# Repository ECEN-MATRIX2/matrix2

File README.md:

# ECEN 403/404 Matrix 2 Electric Scooter

Shared repository for the Matrix 2 ECEN 403/404 senior design project.

## Repository structure

```text
firmware/
  comms/esp32/ESP32_MATRIX2_minimal_reader/  ESP32 comms board firmware
  motor/stm32/                             STM32 motor controller firmware (placeholder)
software/
  mobile-app/scooter-app/                   Mobile application
hardware/
  fpga/                                    FPGA PCB files (placeholder)
  motor/                                   Motor controller PCB files (placeholder)
  comms/                                   Comms board KiCad project
  matrix/                                  Matrix converter hardware and design files
```

The matrix hardware folder includes the existing ECEN 403 and 404 schematics and layouts, simulations, and transformer design documents.

Run mobile app commands from `software/mobile-app/scooter-app`.

## Team workflow

Create a branch for future work, commit your changes, and open a pull request before merging into `main`.

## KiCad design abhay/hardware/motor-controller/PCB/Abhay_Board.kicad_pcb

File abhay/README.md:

# Abhay - motor control and power distribution

| Folder | Contents |
| --- | --- |
| `firmware/NIU_Throttle_Comms_v4_3` | STM32F405 motor firmware, local GUI, tests and v4.3 binary |
| `firmware/NIU_ESP_Comms_v4_3` | Matching ESP32-S3 UART/BLE firmware and app protocol |
| `hardware/rev-o` | Rev O intermediate board: editable KiCad project, libraries, 3D models, BOM and manufacturing files |
| `hardware/motor-controller` | Final motor-control PCB and its original license |

## Working with this folder

Edit these repository copies for future revisions. The original lab folders are separate copies; edits there do not automatically appear here. In GitHub Desktop, select Matrix 2, review changes, commit, push the branch and open a pull request. Keep shared team files outside `abhay/` unchanged unless coordinating a team update.

## Firmware

These are the paired v4.3 sources, with sampled phase-current throttle control and acknowledged app fault-clear/enable commands. This firmware is not FOC. The ESP copy here is the matching motor-integration baseline; it does not replace the team's separate `firmware/comms/` project.

Open either firmware directory in VS Code with PlatformIO, or run `pio run` from that directory. This builds only. The STM32 project targets `genericSTM32F405RG`; the ESP project targets `esp32-s3-devkitc-1` with 4 MB flash. PlatformIO installs the pinned dependencies. The ESP's workstation-specific cache directory override was removed.

Run `python firmware/run_checks.py` for offline native and GUI tests. It needs Python 3 with Tkinter and a C++17 compiler (`g++` on PATH, or set `CXX` to its full path). No boards are accessed. The original `verification/verify.py` files are historical preservation audits: they additionally require older development folders not included in this repository. Use `run_checks.py` for checks in this clone.

Launch the local motor GUI with `firmware/NIU_Throttle_Comms_v4_3/Start Motor GUI.cmd`. Its hardware connection uses ST-Link/OpenOCD; see the project tools and `APP_CONTRACT.txt`. No firmware was flashed as part of this import.

The original release notes/manifests record the state at packaging time and are retained unchanged. The `binary/` folders contain the existing release binaries, not fresh builds from this import. ELF debug files, build caches and serial logs are omitted; the ESP historical manifest still lists the omitted ELF's checksum. Hardware validation is not implied by offline test results. The recent bench discrepancy between indicated supply voltage and MCU VM telemetry remains unresolved; this import does not change VM scaling or safety limits.

## KiCad

Use KiCad 9 and install its standard symbol, footprint and 3D-model libraries.

- Rev O: open `hardware/rev-o/NIU_Intermediate_RevO.kicad_pro`. Gerbers and drill files are in `Manufacturing/Gerbers`; assembly files are in `Manufacturing/Assembly`; the full purchasing BOM is in `Purchasing`. Read `FABRICATION.txt` and `BENCH_CHECKS.txt` before fabrication/assembly. Stock records and validation reports are dated snapshots.
- Motor controller: open `hardware/motor-controller/PCB/Abhay_Board.kicad_pro`. Electrical design and layout are unchanged. Only the two local library-table paths were corrected to the supplied `Abhay.pretty` and `Abhay.lib` files. The board references both `KICAD6_3DMODEL_DIR` and `KICAD9_3DMODEL_DIR`; configure the older variable to the installed standard 3D-model directory if needed.

The motor controller's inherited license and upstream README are included in its folder. Statements in the upstream README describe the original xESC project, not validation or ratings of this modified motor board or the current firmware.

`import_manifest.json` lists SHA-256 checksums for the imported source files and identifies the three packaging-only changes. No motor runtime source, PCB or schematic was changed.

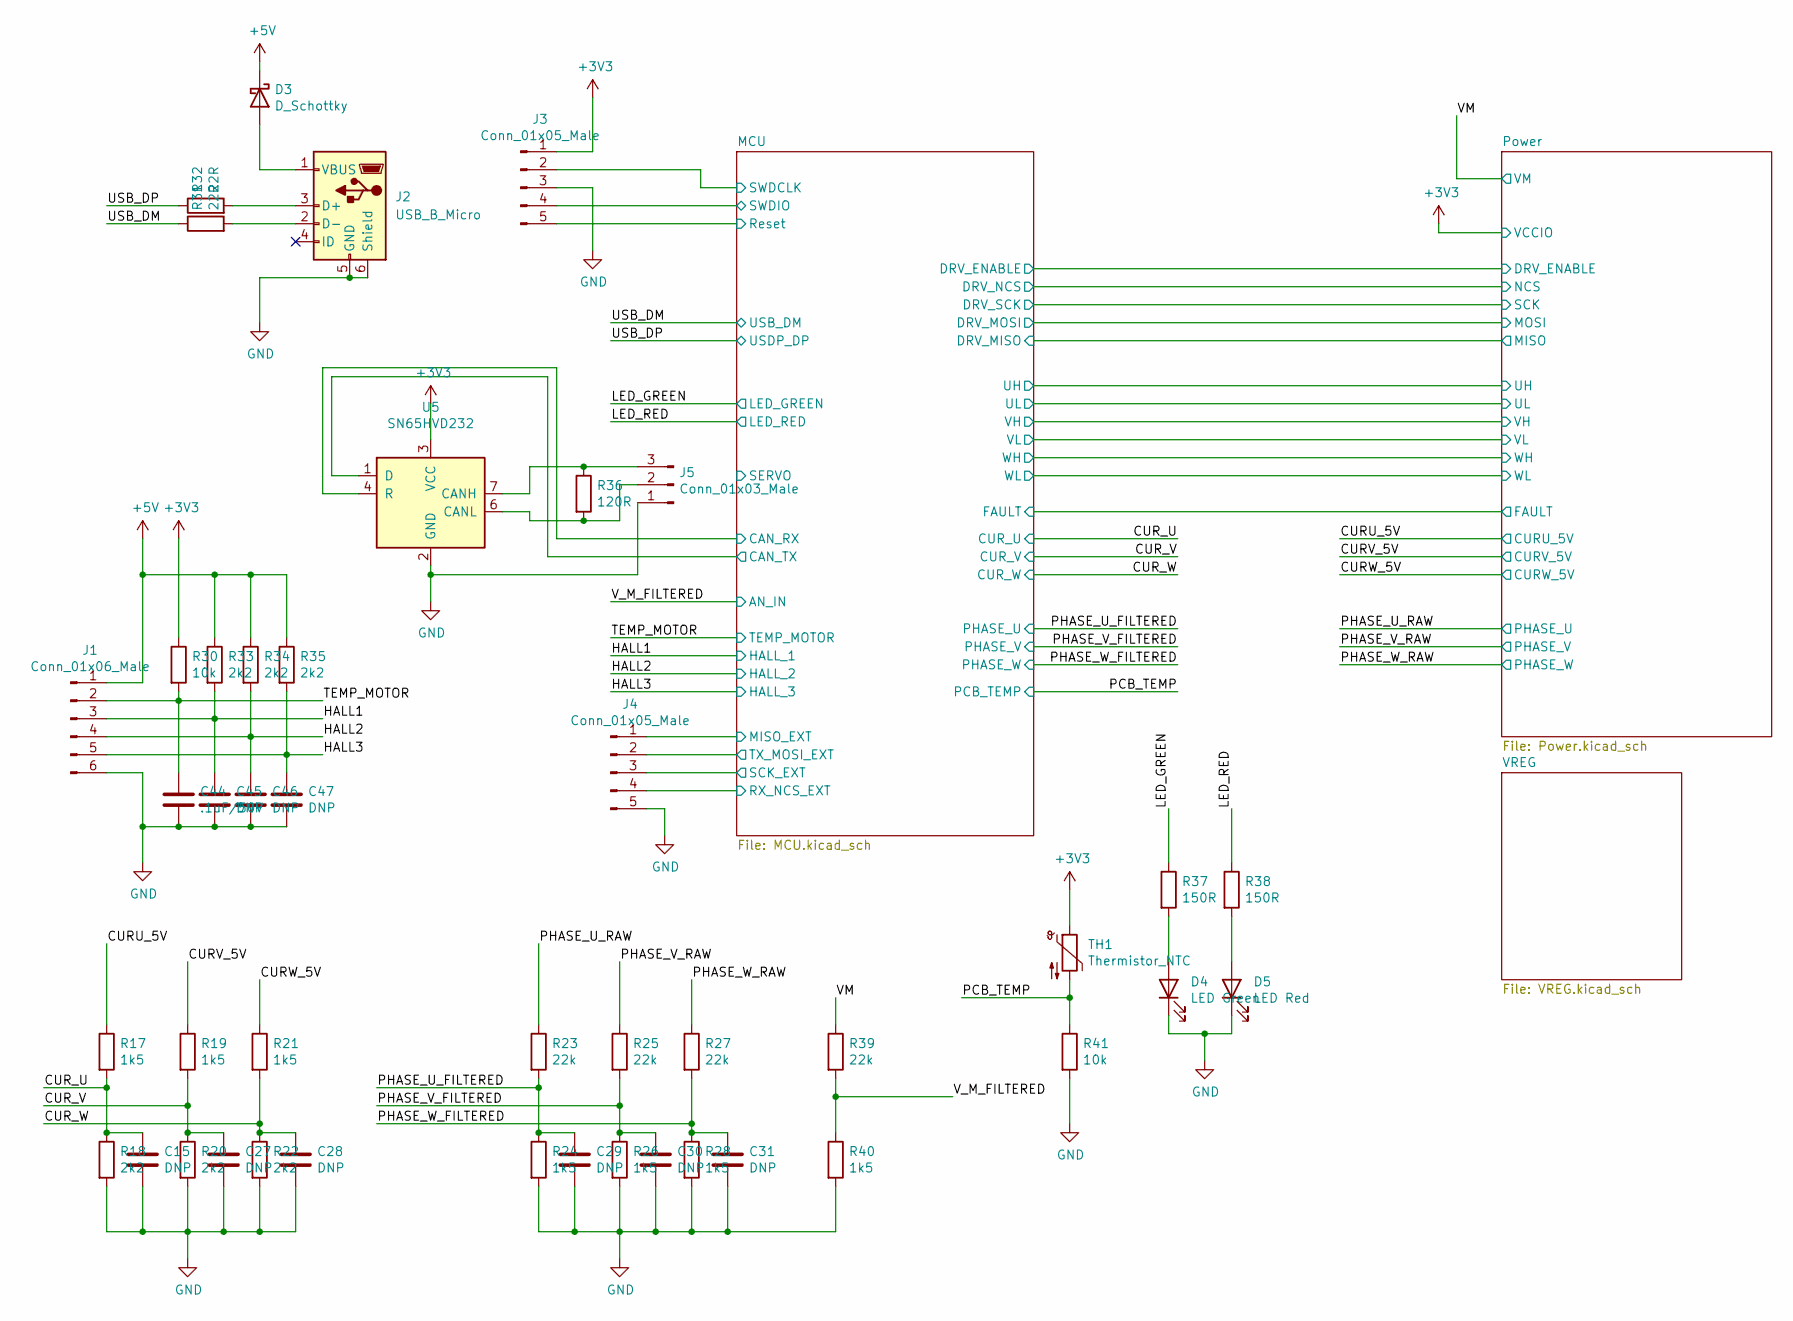
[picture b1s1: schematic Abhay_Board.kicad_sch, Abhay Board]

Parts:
C15, C27, C28, C29, C30, C31, C45, C46, C47: DNP; C_0603_1608Metric
C44: .1uF/50V; C_0603_1608Metric; Part Number CL10B104KC8NNNC; Digikey 1276-1935-1-ND
D3: D_Schottky; D_SOD-123; Part Number PMEG2010ER,115; Digikey 1727-5192-1-ND
D4: LED Green; LED_0603_1608Metric; Part Number LTST-C191KGKT; Digikey 160-1446-1-ND
D5: LED Red; LED_0603_1608Metric; Part Number LTST-C191KRKT; Digikey 160-1447-1-ND
J1: Conn_01x06_Male; PinHeader_1x06_P2.54mm_Vertical; Part Number DZ254R-11-06-63; LCSC C2935912
J2: USB_B_Micro; USB_Micro; JLC C145795
J3, J4: Conn_01x05_Male; PinHeader_1x05_P2.54mm_Vertical; Part Number DZ254R-11-05-63; LCSC C2935911
J5: Conn_01x03_Male; PinHeader_1x03_P2.54mm_Vertical; Part Number DZ254R-11-05-63; LCSC C2935909
R17, R19, R21, R24, R26, R28, R40: 1k5; R_0603_1608Metric; Part Number RC0603FR-071K5L; Digikey 311-1.50KHRCT-ND
R18, R20, R22, R33, R34, R35: 2k2; R_0603_1608Metric; Part Number RC0603FR-072K2L; Digikey 311-2.20KHRCT-ND
R23, R25, R27, R39: 22k; R_0603_1608Metric; Part Number RMCF0603FT22K0; Digikey RMCF0603FT22K0CT-ND
R30, R41: 10k; R_0603_1608Metric; Part Number RC0603FR-0710KL; Digikey 311-10.0KHRCT-ND
R31, R32: 22R; R_0603_1608Metric; Part Number RMCF0603FT22R0; Digikey RMCF0603FT22R0CT-ND
R36: 120R; R_0603_1608Metric; Part Number RMCF0603FT120R; Digikey RMCF0603FT120RCT-ND
R37, R38: 150R; R_0603_1608Metric; Part Number RC0603FR-07150RL; Digikey 311-150HRCT-ND
TH1: Thermistor_NTC; R_0603_1608Metric; Part Number NCU18XH103F60RB; Digikey 490-16279-1-ND
U5: SN65HVD232; SOIC-8_3.9x4.9mm_P1.27mm; Part Number SN65HVD232; Digikey 296-12282-5-ND

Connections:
+3V3: J3.1, R30.1, TH1.1, U5.3 (VCC); also elsewhere on the board
+5V: D3.1 (K), J1.1, R33.1, R34.1, R35.1; also elsewhere on the board
/CURU_5V: R17.1; also elsewhere on the board
/CURV_5V: R19.1; also elsewhere on the board
/CURW_5V: R21.1; also elsewhere on the board
/CUR_U: C15.1, R17.2, R18.1; also elsewhere on the board
/CUR_V: C27.1, R19.2, R20.1; also elsewhere on the board
/CUR_W: C28.1, R21.2, R22.1; also elsewhere on the board
/HALL1: C45.1, J1.3, R33.2; also elsewhere on the board
/HALL2: C46.1, J1.4, R34.2; also elsewhere on the board
/HALL3: C47.1, J1.5, R35.2; also elsewhere on the board
/LED_GREEN: R37.1; also elsewhere on the board
/LED_RED: R38.1; also elsewhere on the board
/MCU/CAN_RX: U5.4 (R); also elsewhere on the board
/MCU/CAN_TX: U5.1 (D); also elsewhere on the board
/MCU/MISO_EXT: J4.1; also elsewhere on the board
/MCU/RX_NCS_EXT: J4.4; also elsewhere on the board
/MCU/Reset: J3.5; also elsewhere on the board
/MCU/SCK_EXT: J4.3; also elsewhere on the board
/MCU/SWDCLK: J3.2; also elsewhere on the board
/MCU/SWDIO: J3.4; also elsewhere on the board
/MCU/TX_MOSI_EXT: J4.2; also elsewhere on the board
/PCB_TEMP: R41.1, TH1.2; also elsewhere on the board
/PHASE_U_FILTERED: C29.1, R23.2, R24.1; also elsewhere on the board
/PHASE_U_RAW: R23.1; also elsewhere on the board
/PHASE_V_FILTERED: C30.1, R25.2, R26.1; also elsewhere on the board
/PHASE_V_RAW: R25.1; also elsewhere on the board
/PHASE_W_FILTERED: C31.1, R27.2, R28.1; also elsewhere on the board
/PHASE_W_RAW: R27.1; also elsewhere on the board
/TEMP_MOTOR: C44.1, J1.2, R30.2; also elsewhere on the board
/USB_DM: R31.1; also elsewhere on the board
/USB_DP: R32.1; also elsewhere on the board
/VM: R39.1; also elsewhere on the board
/V_M_FILTERED: R39.2, R40.1; also elsewhere on the board
GND: C15.2, C27.2, C28.2, C29.2, C30.2, C31.2, C44.2, C45.2, C46.2, C47.2, D4.1 (K), D5.1 (K), J1.6, J2.5 (GND), J2.6 (Shield), J3.3, J4.5, J5.1, R18.2, R20.2, R22.2, R24.2, R26.2, R28.2, R40.2, R41.2, U5.2 (GND); also elsewhere on the board
unnamed: D3.2 (A), J2.1 (VBUS)
unnamed: D4.2 (A), R37.2
unnamed: D5.2 (A), R38.2
unnamed: J2.3 (D+), R32.2
unnamed: J2.2 (D-), R31.2
unnamed: J5.2, R36.2, U5.6 (CANL)
unnamed: J5.3, R36.1, U5.7 (CANH)

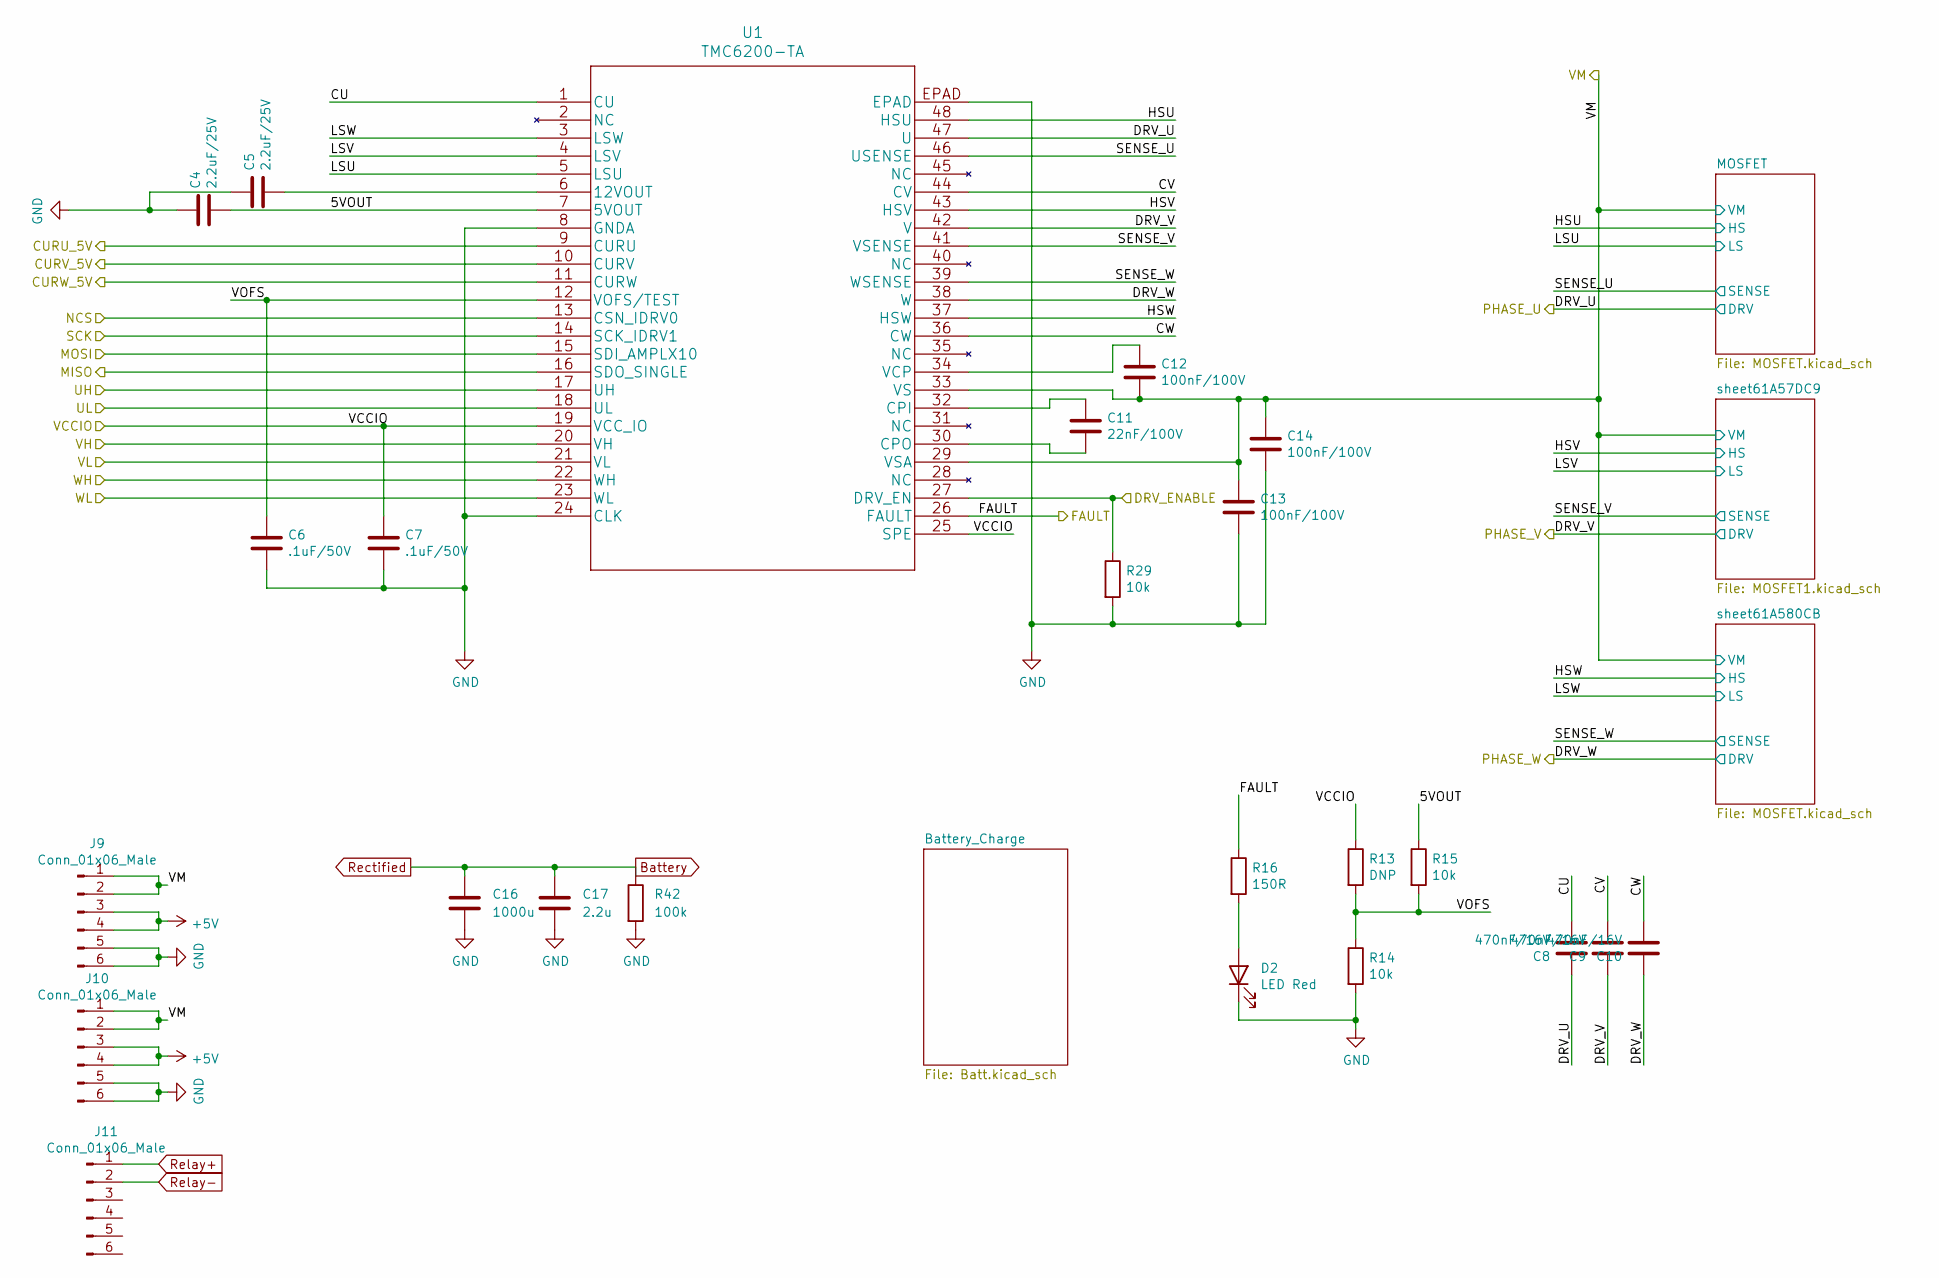
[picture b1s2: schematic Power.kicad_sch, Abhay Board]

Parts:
C4, C5: 2.2uF/25V; C_0805_2012Metric; Part Number GRM21BR71E225KE11L; Digikey 490-14467-1-ND
C6, C7: .1uF/50V; C_0603_1608Metric; Part Number CL10B104KC8NNNC; Digikey 1276-1935-1-ND
C8, C9, C10: 470nF/16V; C_0603_1608Metric; Part Number CL10B474KO8NNNC; Digikey 1276-1062-1-ND
C11: 22nF/100V; C_0603_1608Metric; Part Number C0603C223K1RAC7867; Digikey 399-C0603C223K1RAC7867CT-ND
C12, C13, C14: 100nF/100V; C_0805_2012Metric; Part Number HMK212BJ104KG-T; JLC C28233
C16: 1000u; C_Radial_D18.0mm_H35.5mm_P7.50mm
C17: 2.2u; C_Axial_L3.8mm_D2.6mm_P10.00mm_Horizontal
D2: LED Red; LED_0603_1608Metric; Part Number LTST-C191KRKT; Digikey 160-1447-1-ND
J9, J10, J11: Conn_01x06_Male; PinHeader_1x06_P2.54mm_Vertical; Part Number DZ254R-11-06-63; LCSC C2935912
R13: DNP; R_0603_1608Metric
R14, R15, R29: 10k; R_0603_1608Metric; Part Number RC0603FR-0710KL; Digikey 311-10.0KHRCT-ND
R16: 150R; R_0603_1608Metric; Part Number RC0603FR-07150RL; Digikey 311-150HRCT-ND
R42: 100k; R_Axial_DIN0204_L3.6mm_D1.6mm_P5.08mm_Horizontal
U1: TMC6200-TA; Part Number TMC6200-TA; Digikey 1460-1384-ND

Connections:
+3V3: C7.1, R13.1, U1.19 (VCC_IO), U1.25 (SPE); also elsewhere on the board
+5V: J9.3, J9.4, J10.3, J10.4; also elsewhere on the board
/CURU_5V: U1.9 (CURU); also elsewhere on the board
/CURV_5V: U1.10 (CURV); also elsewhere on the board
/CURW_5V: U1.11 (CURW); also elsewhere on the board
/MCU/DRV_ENABLE: R29.1, U1.27 (DRV_EN); also elsewhere on the board
/MCU/DRV_MISO: U1.16 (SDO_SINGLE); also elsewhere on the board
/MCU/DRV_MOSI: U1.15 (SDI_AMPLX10); also elsewhere on the board
/MCU/DRV_NCS: U1.13 (CSN_IDRV0); also elsewhere on the board
/MCU/DRV_SCK: U1.14 (SCK_IDRV1); also elsewhere on the board
/MCU/UH: U1.17 (UH); also elsewhere on the board
/MCU/UL: U1.18 (UL); also elsewhere on the board
/MCU/VH: U1.20 (VH); also elsewhere on the board
/MCU/VL: U1.21 (VL); also elsewhere on the board
/MCU/WH: U1.22 (WH); also elsewhere on the board
/MCU/WL: U1.23 (WL); also elsewhere on the board
/PHASE_U_RAW: C8.1, U1.47 (U); also elsewhere on the board
/PHASE_V_RAW: C9.1, U1.42 (V); also elsewhere on the board
/PHASE_W_RAW: C10.1, U1.38 (W); also elsewhere on the board
/Power/5VOUT: C4.2, R15.1, U1.7 (5VOUT)
/Power/CU: C8.2, U1.1 (CU)
/Power/CV: C9.2, U1.44 (CV)
/Power/CW: C10.2, U1.36 (CW)
/Power/FAULT: R16.1, U1.26 (FAULT); also elsewhere on the board
/Power/HSU: U1.48 (HSU); also elsewhere on the board
/Power/HSV: U1.43 (HSV); also elsewhere on the board
/Power/HSW: U1.37 (HSW); also elsewhere on the board
/Power/LSU: U1.5 (LSU); also elsewhere on the board
/Power/LSV: U1.4 (LSV); also elsewhere on the board
/Power/LSW: U1.3 (LSW); also elsewhere on the board
/Power/SENSE_U: U1.46 (USENSE); also elsewhere on the board
/Power/SENSE_V: U1.41 (VSENSE); also elsewhere on the board
/Power/SENSE_W: U1.39 (WSENSE); also elsewhere on the board
/Power/VOFS: C6.1, R13.2, R14.1, R15.2, U1.12 (VOFS/TEST)
/VM: C12.2, C13.1, C14.1, J9.1, J9.2, J10.1, J10.2, U1.29 (VSA), U1.33 (VS); also elsewhere on the board
Battery: C16.1, C17.1, R42.1; also elsewhere on the board
GND: C4.1, C5.1, C6.2, C7.2, C13.2, C14.2, C16.2, C17.2, D2.1 (K), J9.5, J9.6, J10.5, J10.6, R14.2, R29.2, R42.2, U1.8 (GNDA), U1.24 (CLK), U1.EPAD; also elsewhere on the board
unnamed: D2.2 (A), R16.2
unnamed: C5.2, U1.6 (12VOUT)
unnamed: C11.2, U1.32 (CPI)
unnamed: C11.1, U1.30 (CPO)
unnamed: C12.1, U1.34 (VCP)
Relay+: J11.1; also elsewhere on the board
Relay-: J11.2; also elsewhere on the board

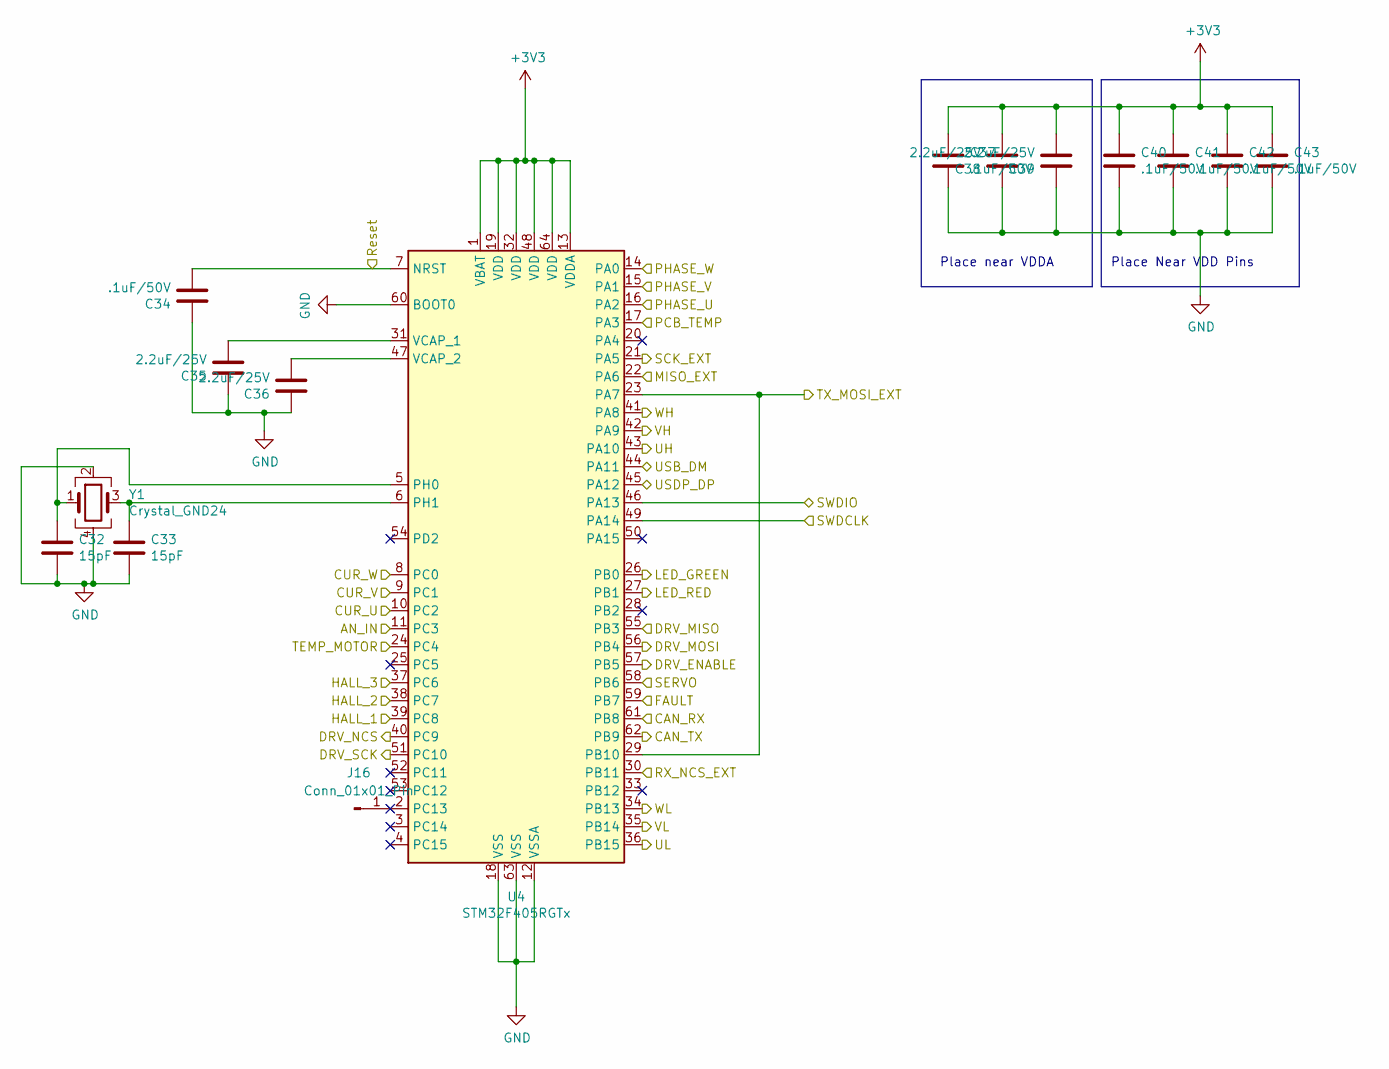
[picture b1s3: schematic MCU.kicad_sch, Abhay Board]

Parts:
C32, C33: 15pF; C_0603_1608Metric; Part Number GRM1885C2A150JA01D; Digikey 490-1331-1-ND
C34, C37, C40, C41, C42, C43: .1uF/50V; C_0603_1608Metric; Part Number CL10B104KC8NNNC; Digikey 1276-1935-1-ND
C35, C36, C38, C39: 2.2uF/25V; C_0805_2012Metric; Part Number GRM21BR71E225KE11L; Digikey 490-14467-1-ND
J16: Conn_01x01_Pin; PinHeader_1x01_P1.00mm_Vertical
U4: STM32F405RGTx; LQFP-64_10x10mm_P0.5mm; Part Number STM32F405RGTx; LCSC C15742
Y1: Crystal_GND24; Crystal_SMD_3225-4Pin_3.2x2.5mm; Part Number ECS-80-12-33-JGN-TR; Digikey 50-ECS-80-12-33-JGN-CT-ND

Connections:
+3V3: C37.1, C38.2, C39.2, C40.1, C41.1, C42.1, C43.1, U4.1 (VBAT), U4.13 (VDDA), U4.19 (VDD), U4.32 (VDD), U4.48 (VDD), U4.64 (VDD); also elsewhere on the board
/CUR_U: U4.10 (PC2); also elsewhere on the board
/CUR_V: U4.9 (PC1); also elsewhere on the board
/CUR_W: U4.8 (PC0); also elsewhere on the board
/HALL1: U4.39 (PC8); also elsewhere on the board
/HALL2: U4.38 (PC7); also elsewhere on the board
/HALL3: U4.37 (PC6); also elsewhere on the board
/LED_GREEN: U4.26 (PB0); also elsewhere on the board
/LED_RED: U4.27 (PB1); also elsewhere on the board
/MCU/CAN_RX: U4.61 (PB8); also elsewhere on the board
/MCU/CAN_TX: U4.62 (PB9); also elsewhere on the board
/MCU/DRV_ENABLE: U4.57 (PB5); also elsewhere on the board
/MCU/DRV_MISO: U4.55 (PB3); also elsewhere on the board
/MCU/DRV_MOSI: U4.56 (PB4); also elsewhere on the board
/MCU/DRV_NCS: U4.40 (PC9); also elsewhere on the board
/MCU/DRV_SCK: U4.51 (PC10); also elsewhere on the board
/MCU/MISO_EXT: U4.22 (PA6); also elsewhere on the board
/MCU/RX_NCS_EXT: U4.30 (PB11); also elsewhere on the board
/MCU/Reset: C34.2, U4.7 (NRST); also elsewhere on the board
/MCU/SCK_EXT: U4.21 (PA5); also elsewhere on the board
/MCU/SERVO: U4.58 (PB6)
/MCU/SWDCLK: U4.49 (PA14); also elsewhere on the board
/MCU/SWDIO: U4.46 (PA13); also elsewhere on the board
/MCU/TX_MOSI_EXT: U4.23 (PA7), U4.29 (PB10); also elsewhere on the board
/MCU/UH: U4.43 (PA10); also elsewhere on the board
/MCU/UL: U4.36 (PB15); also elsewhere on the board
/MCU/VH: U4.42 (PA9); also elsewhere on the board
/MCU/VL: U4.35 (PB14); also elsewhere on the board
/MCU/WH: U4.41 (PA8); also elsewhere on the board
/MCU/WL: U4.34 (PB13); also elsewhere on the board
/PCB_TEMP: U4.17 (PA3); also elsewhere on the board
/PHASE_U_FILTERED: U4.16 (PA2); also elsewhere on the board
/PHASE_V_FILTERED: U4.15 (PA1); also elsewhere on the board
/PHASE_W_FILTERED: U4.14 (PA0); also elsewhere on the board
/Power/FAULT: U4.59 (PB7); also elsewhere on the board
/TEMP_MOTOR: U4.24 (PC4); also elsewhere on the board
/USB_DM: U4.44 (PA11); also elsewhere on the board
/USB_DP: U4.45 (PA12); also elsewhere on the board
/V_M_FILTERED: U4.11 (PC3); also elsewhere on the board
GND: C32.2, C33.2, C34.1, C35.1, C36.1, C37.2, C38.1, C39.1, C40.2, C41.2, C42.2, C43.2, U4.12 (VSSA), U4.18 (VSS), U4.60 (BOOT0), U4.63 (VSS), Y1.2, Y1.4; also elsewhere on the board
unnamed: C32.1, U4.5 (PH0), Y1.1
unnamed: C33.1, U4.6 (PH1), Y1.3
unnamed: C35.2, U4.31 (VCAP_1)
unnamed: C36.2, U4.47 (VCAP_2)

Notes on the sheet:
Place Near VDD Pins
Place near VDDA

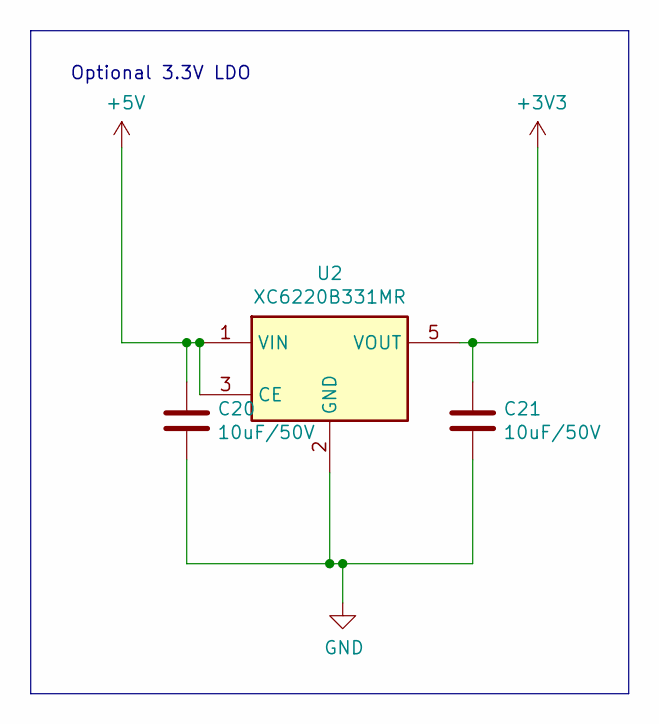
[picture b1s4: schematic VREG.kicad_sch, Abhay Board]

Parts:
C20, C21: 10uF/50V; C_1206_3216Metric; Part Number CL31A106KAHNNNE; Digikey 1276-1075-1-ND
U2: XC6220B331MR; SOT-23-5; Part Number XC6220B331MR; Digikey 893-1133-1-ND

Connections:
+3V3: C21.1, U2.5 (VOUT); also elsewhere on the board
+5V: C20.1, U2.1 (VIN), U2.3 (CE); also elsewhere on the board
GND: C20.2, C21.2, U2.2 (GND); also elsewhere on the board

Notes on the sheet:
Optional 3.3V LDO

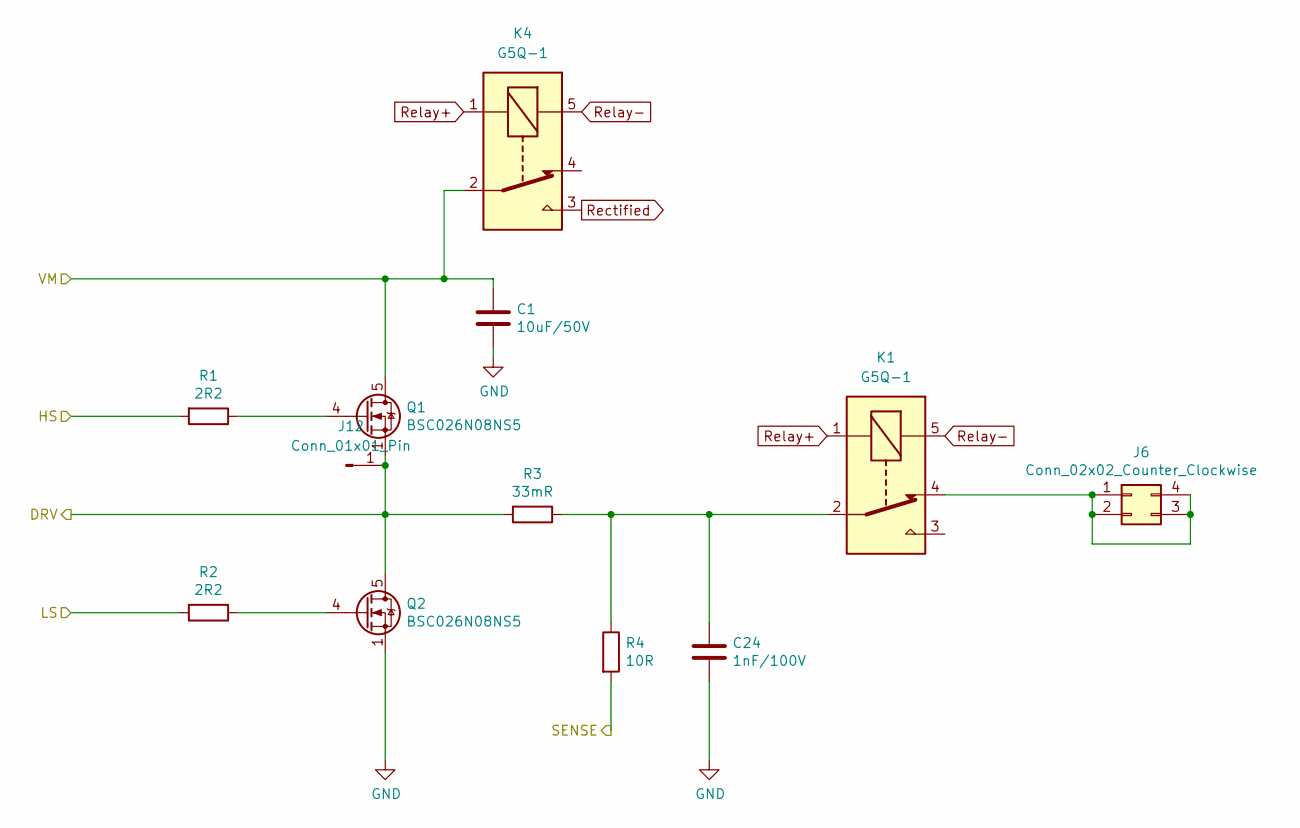
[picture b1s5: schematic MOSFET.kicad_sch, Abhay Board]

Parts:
C1: 10uF/50V; C_1206_3216Metric; Part Number CL31B225KBHVPNE; Digikey 1276-6735-1-ND
C24: 1nF/100V; C_0603_1608Metric; Part Number GCM188R72A102KA37D; Digikey 490-4780-1-ND
J6: Conn_02x02_Counter_Clockwise; PinHeader_2x02_P2.54mm_Vertical; Part Number B-2100S04P-B110; LCSC C124362
J12: Conn_01x01_Pin; PinHeader_1x01_P1.00mm_Vertical
K1, K4: G5Q-1; Relay_SPDT_Omron-G5Q-1
Q1, Q2: BSC026N08NS5; TDSON-8-1; Part Number BSC026N08NS5; Digikey BSC026N08NS5ATMA1CT-ND
R1, R2: 2R2; R_0603_1608Metric; Part Number ERJ-3GEYJ2R2V; Digikey P2.2GCT-ND
R3: 33mR; R_2512_6332Metric; Part Number ARP2512GJR033; LCSC C2903495
R4: 10R; R_0603_1608Metric; Part Number RMCF0603FT10R0; Digikey RMCF0603FT10R0CT-ND

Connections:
/PHASE_U_RAW: J12.1, Q1.1 (S), Q1.2 (S), Q1.3 (S), Q2.5 (D), R3.2; also elsewhere on the board
/Power/HSU: R1.2; also elsewhere on the board
/Power/LSU: R2.2; also elsewhere on the board
/Power/SENSE_U: R4.2; also elsewhere on the board
/VM: C1.1, K4.2, Q1.5 (D); also elsewhere on the board
Battery: K4.3; also elsewhere on the board
GND: C1.2, C24.2, Q2.1 (S), Q2.2 (S), Q2.3 (S); also elsewhere on the board
unnamed: C24.1, K1.2, R3.1, R4.1
unnamed: J6.1, J6.2, J6.3, J6.4, K1.4
unnamed: Q1.4 (G), R1.1
unnamed: Q2.4 (G), R2.1
Relay+: K1.1, K4.1; also elsewhere on the board
Relay-: K1.5, K4.5; also elsewhere on the board

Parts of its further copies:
C3: 10uF/50V; C_1206_3216Metric; Part Number CL31B225KBHVPNE; Digikey 1276-6735-1-ND
C26: 1nF/100V; C_0603_1608Metric; Part Number GCM188R72A102KA37D; Digikey 490-4780-1-ND
J8: Conn_02x02_Counter_Clockwise; PinHeader_2x02_P2.54mm_Vertical; Part Number B-2100S04P-B110; LCSC C124362
J13: Conn_01x01_Pin; PinHeader_1x01_P1.00mm_Vertical
K3, K6: G5Q-1; Relay_SPDT_Omron-G5Q-1
Q5, Q6: BSC026N08NS5; TDSON-8-1; Part Number BSC026N08NS5; Digikey BSC026N08NS5ATMA1CT-ND
R9, R10: 2R2; R_0603_1608Metric; Part Number ERJ-3GEYJ2R2V; Digikey P2.2GCT-ND
R11: 33mR; R_2512_6332Metric; Part Number ARP2512GJR033; LCSC C2903495
R12: 10R; R_0603_1608Metric; Part Number RMCF0603FT10R0; Digikey RMCF0603FT10R0CT-ND

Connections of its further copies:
/PHASE_W_RAW: J13.1, Q5.1 (S), Q5.2 (S), Q5.3 (S), Q6.5 (D), R11.2; also elsewhere on the board
/Power/HSW: R9.2; also elsewhere on the board
/Power/LSW: R10.2; also elsewhere on the board
/Power/SENSE_W: R12.2; also elsewhere on the board
/VM: C3.1, K6.2, Q5.5 (D); also elsewhere on the board
Battery: K6.3; also elsewhere on the board
GND: C3.2, C26.2, Q6.1 (S), Q6.2 (S), Q6.3 (S); also elsewhere on the board
unnamed: C26.1, K3.2, R11.1, R12.1
unnamed: J8.1, J8.2, J8.3, J8.4, K3.4
unnamed: Q5.4 (G), R9.1
unnamed: Q6.4 (G), R10.1
Relay+: K3.1, K6.1; also elsewhere on the board
Relay-: K3.5, K6.5; also elsewhere on the board

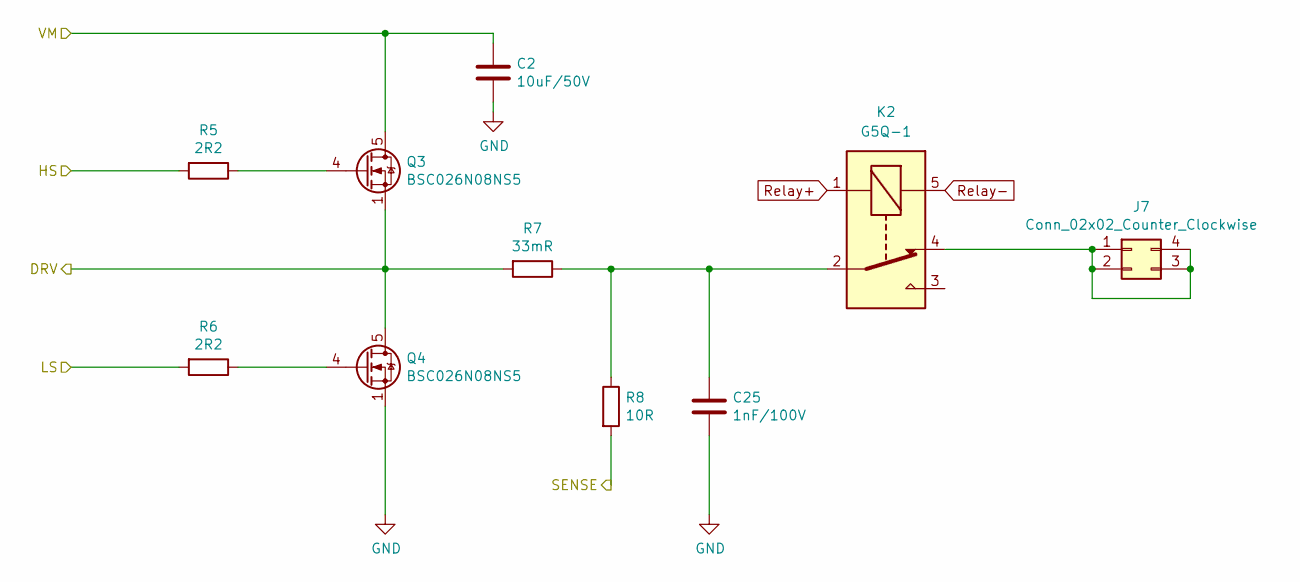
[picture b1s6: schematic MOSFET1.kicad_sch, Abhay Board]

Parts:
C2: 10uF/50V; C_1206_3216Metric; Part Number CL31B225KBHVPNE; Digikey 1276-6735-1-ND
C25: 1nF/100V; C_0603_1608Metric; Part Number GCM188R72A102KA37D; Digikey 490-4780-1-ND
J7: Conn_02x02_Counter_Clockwise; PinHeader_2x02_P2.54mm_Vertical; Part Number B-2100S04P-B110; LCSC C124362
K2: G5Q-1; Relay_SPDT_Omron-G5Q-1
Q3, Q4: BSC026N08NS5; TDSON-8-1; Part Number BSC026N08NS5; Digikey BSC026N08NS5ATMA1CT-ND
R5, R6: 2R2; R_0603_1608Metric; Part Number ERJ-3GEYJ2R2V; Digikey P2.2GCT-ND
R7: 33mR; R_2512_6332Metric; Part Number ARP2512GJR033; LCSC C2903495
R8: 10R; R_0603_1608Metric; Part Number RMCF0603FT10R0; Digikey RMCF0603FT10R0CT-ND

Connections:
/PHASE_V_RAW: Q3.1 (S), Q3.2 (S), Q3.3 (S), Q4.5 (D), R7.2; also elsewhere on the board
/Power/HSV: R5.2; also elsewhere on the board
/Power/LSV: R6.2; also elsewhere on the board
/Power/SENSE_V: R8.2; also elsewhere on the board
/VM: C2.1, Q3.5 (D); also elsewhere on the board
GND: C2.2, C25.2, Q4.1 (S), Q4.2 (S), Q4.3 (S); also elsewhere on the board
unnamed: C25.1, K2.2, R7.1, R8.1
unnamed: J7.1, J7.2, J7.3, J7.4, K2.4
unnamed: Q3.4 (G), R5.1
unnamed: Q4.4 (G), R6.1
Relay+: K2.1; also elsewhere on the board
Relay-: K2.5; also elsewhere on the board

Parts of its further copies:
K3: G5Q-1; Relay_SPDT_Omron-G5Q-1

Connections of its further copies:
unnamed 67: K3.2; also elsewhere on the board
unnamed 103: K3.4; also elsewhere on the board
Relay+: K3.1; also elsewhere on the board
Relay-: K3.5; also elsewhere on the board

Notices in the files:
parts and their libraries:
Copyright 2021 Accelerated Designs. All rights reserved.
